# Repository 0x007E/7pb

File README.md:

# `7PB` - 7-Phase Flasher (7-Phasenblinker)

The `7PB` project is based on a pcb with an array of transistors (`BC547`) that are constantly switching their state while driving leds with different colors.

| Experience | Level |
|:------------|:-----:|
| Soldering   |  |
| Mechanical  |  |

# Downloads

| Type      | File               | Description              |
|:---------:|:------------------:|:-------------------------|
| Simulation | [asc](https://github.com/0x007E/7pb/raw/refs/heads/main/7PB.asc) | LTSpice Simulation | 
| Lochmaster | [lm4](https://github.com/0x007E/7pb/raw/refs/heads/main/7PB.LM4) | Stripe grid circuit board | 
| Schematic | [pdf](https://github.com/0x007E/7pb/releases/latest/download/schematic.pdf) / [cadlab](https://cadlab.io/project/28593/main/files)     | Schematic files          |
| Board     | [pdf](https://github.com/0x007E/7pb/releases/latest/download/pcb.pdf) / [cadlab](https://cadlab.io/project/28593/main/files)     | Board file               |
| Drill     | [pdf](https://github.com/0x007E/7pb/releases/latest/download/drill.pdf) | Drill file               |
| Gerber    | [zip](https://github.com/0x007E/7pb/releases/latest/download/kicad.zip) / [tar](https://github.com/0x007E/7pb/releases/latest/download/kicad.tar.gz)                | Gerber/Drill files       |
| Housing, PCB | [zip](https://github.com/0x007E/7pb/releases/latest/download/freecad.zip) / [tar](https://github.com/0x007E/7pb/releases/latest/download/freecad.tar.gz) | Housing and PCB (STEP) files     |

# Hardware

There are two parts of the hardware. The pcb and the housing of the `7PB`. The pcb is created with `KiCAD` and the housing with `FreeCAD`. All files are built with `github actions` so that they are ready for a production environment. The housing is printed with a 3D-printer (`Dremel 3D40`).

## PCB

The circuit board is populated on one side (Top). The best way for soldering is within a standard soldering system.

### Top Layer

### Bottom Layer

## Mechanical

The housing has a tolerance of `0.2mm` on each side of the case. So the pcb should fit perfectly in the housing. The tolerance can be modified with `FreeCAD` in the `Parameter` Spreadsheet.

### Assembled

#### Exploded

# Additional Information

| Type       | Link               | Description              |
|:----------:|:------------------:|:-------------------------|
| BC547 | [pdf](https://www.sparkfun.com/datasheets/Components/BC546.pdf) | NPN Transistor |

---

R. GAECHTER

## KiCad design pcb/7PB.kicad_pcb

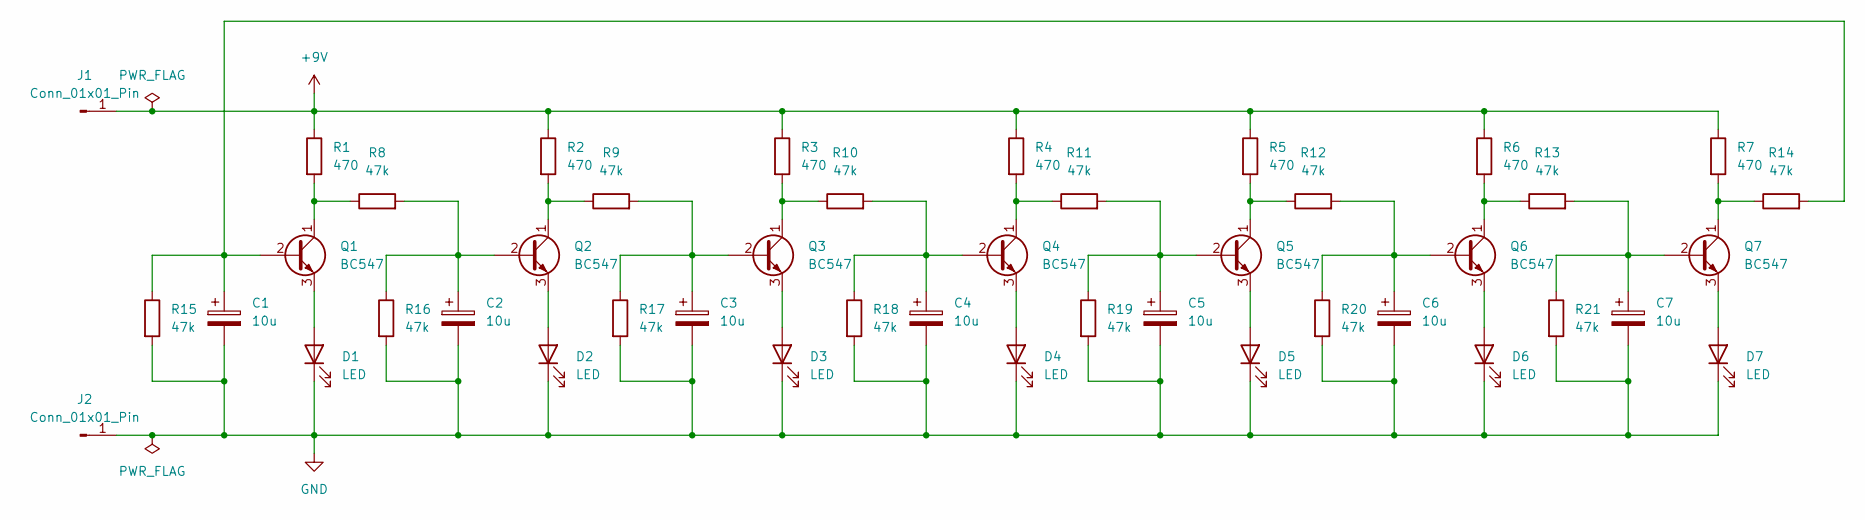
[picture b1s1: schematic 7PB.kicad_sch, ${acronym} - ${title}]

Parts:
C1, C2, C3, C4, C5, C6, C7: 10u; CP_Radial_D5.0mm_P2.50mm
D1, D2, D3, D4, D5, D6, D7: LED; PinSocket_1x02_P2.54mm_Vertical
J1, J2: Conn_01x01_Pin; Pin_D0.9mm_L10.0mm_W2.4mm_FlatFork
Q1, Q2, Q3, Q4, Q5, Q6, Q7: BC547; TO-92_Inline_Wide
R1, R2, R3, R4, R5, R6, R7: 470; R_Axial_DIN0207_L6.3mm_D2.5mm_P10.16mm_Horizontal
R8, R9, R10, R11, R12, R13, R14, R15, R16, R17, R18, R19, R20, R21: 47k; R_Axial_DIN0207_L6.3mm_D2.5mm_P10.16mm_Horizontal

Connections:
+9V: J1.1, R1.1, R2.1, R3.1, R4.1, R5.1, R6.1, R7.1
GND: C1.2, C2.2, C3.2, C4.2, C5.2, C6.2, C7.2, D1.1 (K), D2.1 (K), D3.1 (K), D4.1 (K), D5.1 (K), D6.1 (K), D7.1 (K), J2.1, R15.2, R16.2, R17.2, R18.2, R19.2, R20.2, R21.2
unnamed: D1.2 (A), Q1.3 (E)
unnamed: D2.2 (A), Q2.3 (E)
unnamed: D3.2 (A), Q3.3 (E)
unnamed: D4.2 (A), Q4.3 (E)
unnamed: D5.2 (A), Q5.3 (E)
unnamed: D6.2 (A), Q6.3 (E)
unnamed: D7.2 (A), Q7.3 (E)
unnamed: C1.1, Q1.2 (B), R14.2, R15.1
unnamed: Q1.1 (C), R1.2, R8.1
unnamed: C2.1, Q2.2 (B), R8.2, R16.1
unnamed: Q2.1 (C), R2.2, R9.1
unnamed: C3.1, Q3.2 (B), R9.2, R17.1
unnamed: Q3.1 (C), R3.2, R10.1
unnamed: C4.1, Q4.2 (B), R10.2, R18.1
unnamed: Q4.1 (C), R4.2, R11.1
unnamed: C5.1, Q5.2 (B), R11.2, R19.1
unnamed: Q5.1 (C), R5.2, R12.1
unnamed: C6.1, Q6.2 (B), R12.2, R20.1
unnamed: Q6.1 (C), R6.2, R13.1
unnamed: C7.1, Q7.2 (B), R13.2, R21.1
unnamed: Q7.1 (C), R7.2, R14.1

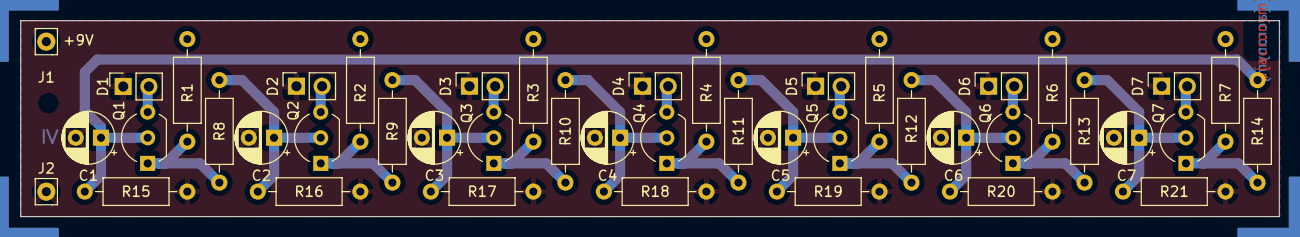
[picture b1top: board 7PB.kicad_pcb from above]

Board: 2 copper layers, 124.7 x 19.4 mm, 44 parts (0 on the bottom side), 23 nets.

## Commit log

2024-10-24 Add README
2024-10-24 Create pipeline

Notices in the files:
README.md:
License CC By-NC-SA
parts and their libraries:
license: CC BY-NC-SA 4.0
